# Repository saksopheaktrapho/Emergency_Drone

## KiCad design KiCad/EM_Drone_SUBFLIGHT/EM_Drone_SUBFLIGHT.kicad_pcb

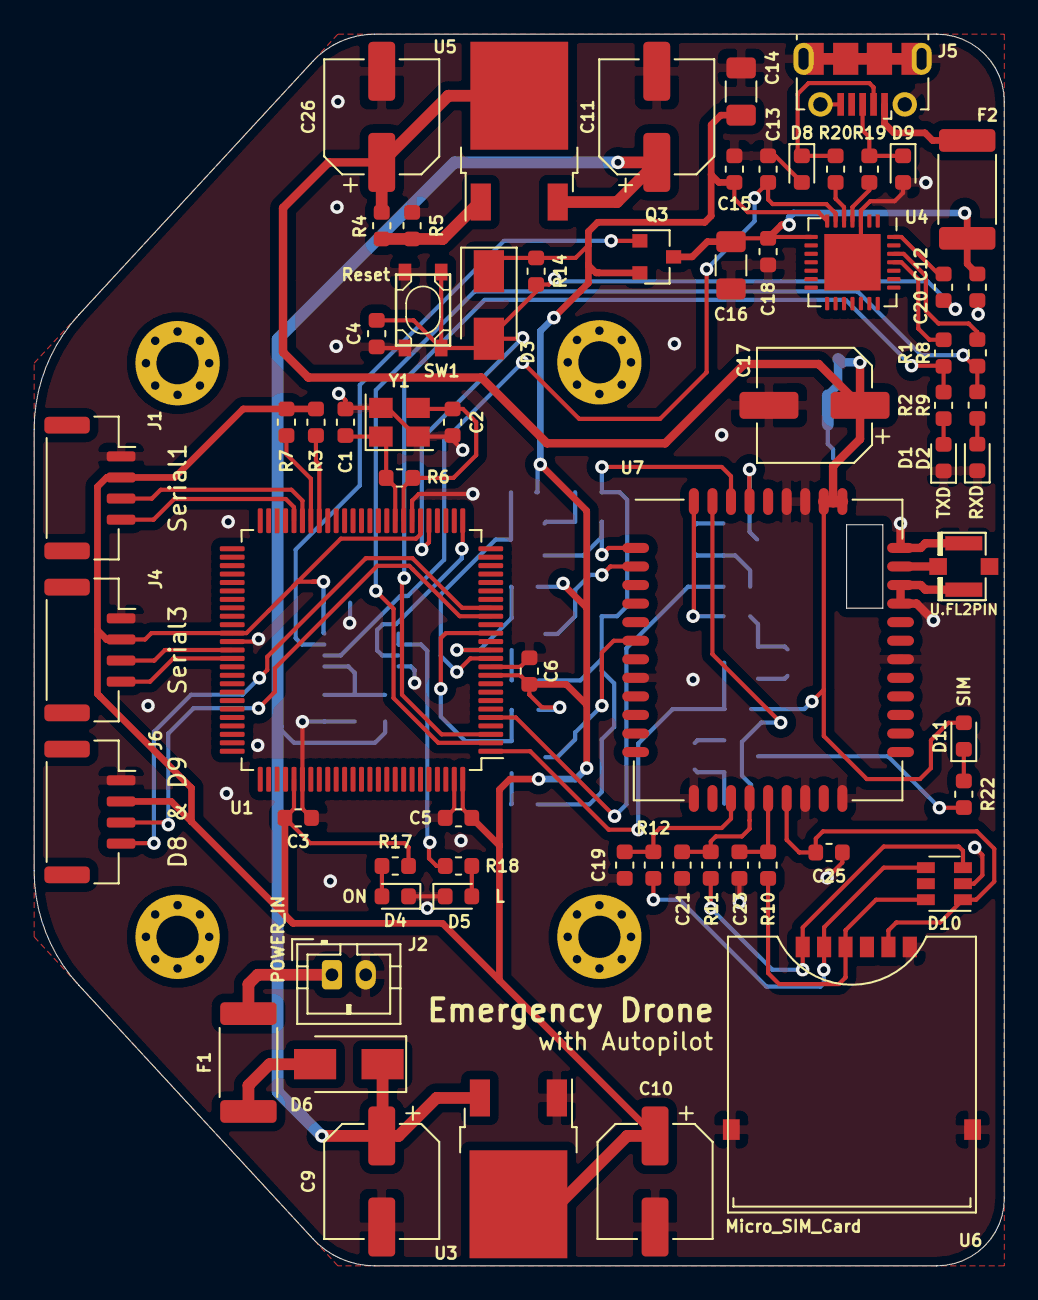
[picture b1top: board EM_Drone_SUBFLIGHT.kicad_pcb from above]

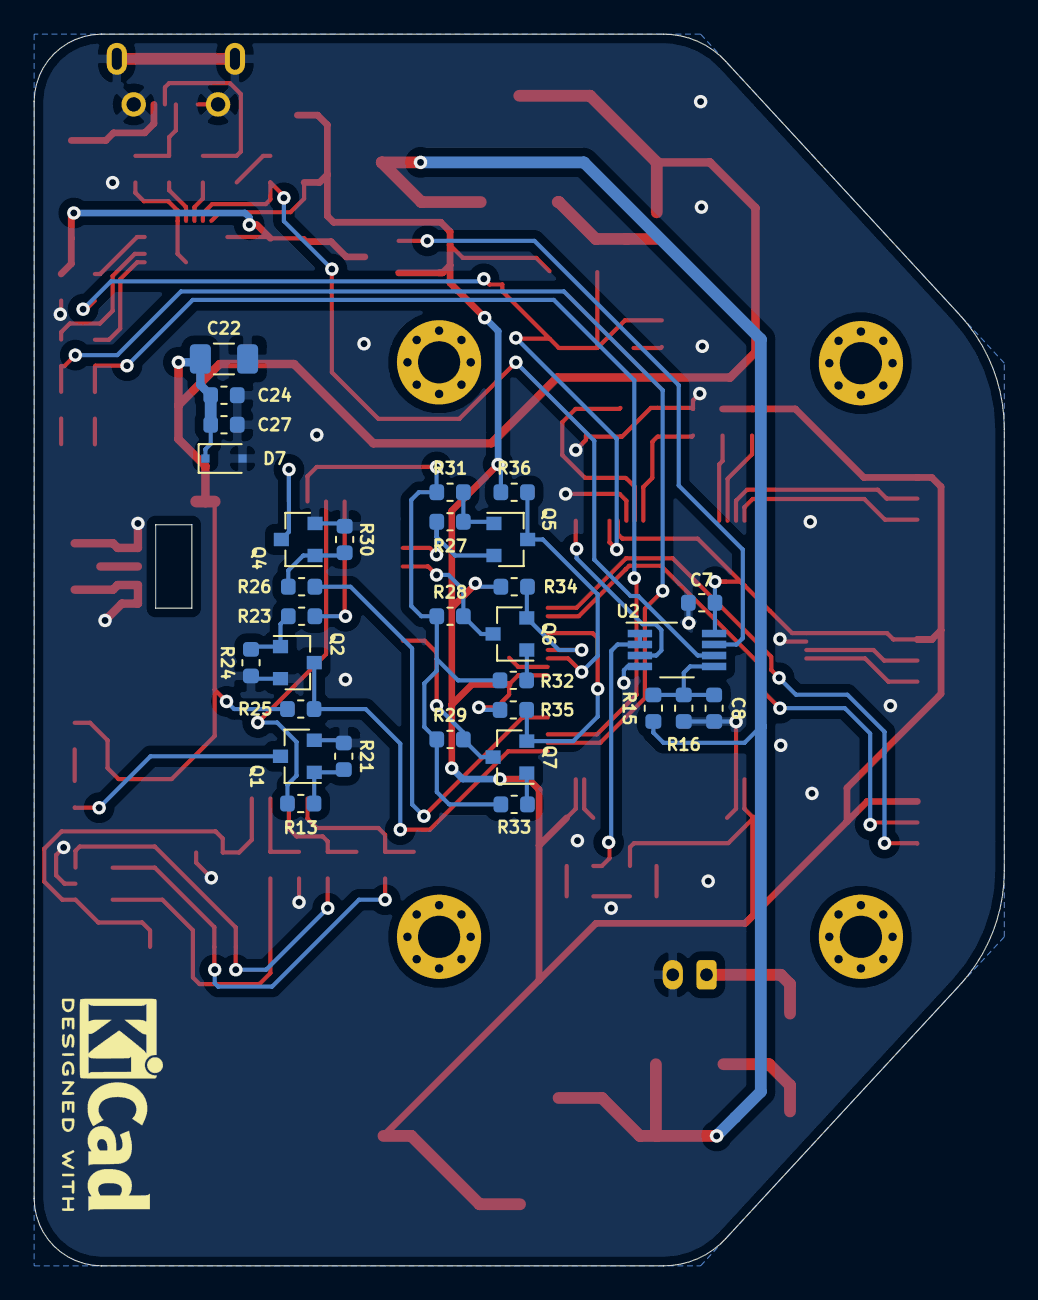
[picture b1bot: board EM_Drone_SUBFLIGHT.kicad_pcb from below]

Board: 2 copper layers, 57.5 x 73.0 mm, 102 parts (31 on the bottom side), 66 nets.

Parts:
C1, C2, C4, C19, C21, C23: 22p; C_0603_1608Metric
C3, C5, C6, C7, C8, C12, C13, C15, C18, C20, C25: 100n; C_0603_1608Metric
C9, C10, C11, C26: 470u; CP_Elec_6.3x7.7
C14, C16: 10u; C_1206_3216Metric
C17: CA_470u; CP_Elec_6.3x7.7
C22: CB_10u; C_1206_3216Metric
C24: 33p; C_0603_1608Metric
C27: 10p; C_0603_1608Metric
D1: TXD; LED_0603_1608Metric
D2: RXD; LED_0603_1608Metric
D3, D6: D; D_SMA
D4: ON; LED_0603_1608Metric
D5: L; LED_0603_1608Metric
D7: D_Zener; D_SOD-323F
D8, D9: ESD; D_0603_1608Metric
D10: ESDA6V1-5SC6; SOT-23-6
D11: SIM; LED_0603_1608Metric
F1: Fuse; Fuse_2512_6332Metric
F2: 0.5A; Fuse_2512_6332Metric
H1, H2, H3, H4: MountingHole; MountingHole_2.5mm_Pad_Via
J1: Telemetry_Port; JST_GH_SM04B-GHS-TB_1x04-1MP_P1.25mm_Horizontal
J2: POWER_IN; JST_PH_B2B-PH-K_1x02_P2.00mm_Vertical
J3: U.FL2PIN; U.FL
J4: Serial3; JST_GH_SM04B-GHS-TB_1x04-1MP_P1.25mm_Horizontal
J5: USB_B_Micro; USB_Micro-B_Molex-105017-0001
J6: IO; JST_GH_SM04B-GHS-TB_1x04-1MP_P1.25mm_Horizontal
Q1, Q2, Q4, Q5, Q6, Q7: 1P; SOT-23
Q3: FDN340P; SOT-23
R1, R2, R8, R9, R17, R18: 1k; R_0603_1608Metric
R3, R5, R7, R13, R23, R26, R28, R29, R31, R32, R33, R36: 4.7k; R_0603_1608Metric
R4: 2k; R_0603_1608Metric
R6: 1M; R_0603_1608Metric
R10, R11, R12: 510; R_0603_1608Metric
R14, R15, R16: 10k; R_0603_1608Metric
R19, R20: 22; R_0603_1608Metric
R21, R24, R27, R30, R34, R35: 47k; R_0603_1608Metric
R22, R25: 470; R_0603_1608Metric
SW1: SW_Push; Button_Switch_3.2x4.2
U1: ATmega2560-16AU; TQFP-100_14x14mm_P0.5mm
U2: LMV358; VSSOP-8_3.0x3.0mm_P0.65mm
U3: LM1084-5.0; TO-252-2
U4: CP2102N-A01-GQFN28; QFN-28-1EP_5x5mm_P0.5mm_EP3.35x3.35mm
U5: LM1084-ADJ; TO-252-2
U6: microSIM_Holder_0181AAAA06A
U7: SIM7020E; SIMCom_SIM800C
Y1: Crystal_GND24; Crystal_SMD_3225-4Pin_3.2x2.5mm

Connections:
+3V3: C13.1, U2.6, U4.6
+5V: C3.1, C5.1, C6.1, C7.1, C10.1, C14.1, C15.1, D3.1, J1.2, J4.2, J6.2, Q3.2, R3.1, R7.1, R14.1, R17.2, R34.1, R35.1, R36.1, U1.10, U1.31, U1.61, U1.80, U1.100, U2.8, U3.2, U4.7
/Arduino_MEGA/D4: Q2.3, R25.2, U1.1
/Arduino_MEGA/D5: R26.2, U1.5
/Arduino_MEGA/D6: Q7.2, R35.2, U1.15
/Arduino_MEGA/D8: J6.3, U1.17
/Arduino_MEGA/D9: J6.4, U1.18
/Arduino_MEGA/PB7: U1.26, U2.3
/Arduino_MEGA/RESET: C4.1, C12.2, D3.2, R14.2, SW1.1, U1.30
/Arduino_MEGA/RX0: R8.1, R9.2, U1.2
/Arduino_MEGA/RXD1: J1.3, U1.45
/Arduino_MEGA/RXD2: Q5.3, R36.2, U1.12
/Arduino_MEGA/RXD3: J4.3, U1.63
/Arduino_MEGA/SCL: R3.2, U1.43
/Arduino_MEGA/SDA: R7.2, U1.44
/Arduino_MEGA/TX0: R1.1, R2.2, U1.3
/Arduino_MEGA/TXD1: J1.4, U1.46
/Arduino_MEGA/TXD3: J4.4, U1.64
/Arduino_MEGA/U_RXD: R1.2, U4.25
/Arduino_MEGA/U_TXD: R8.2, U4.26
/Arduino_MEGA/XTAL1: C1.1, R6.1, U1.34, Y1.1
/Arduino_MEGA/XTAL2: C2.1, R6.2, U1.33, Y1.3
/SIM800c/GSM_ANT: J3.FEED, U7.32
/SIM800c/NETLIGHT: R13.2, U7.41
/SIM800c/PWRKEY: Q4.3, U7.39
/SIM800c/RXD: Q6.2, R34.2, U1.13
/SIM800c/SIM_CLK: C21.1, R11.2, U7.16
/SIM800c/SIM_DATA: C19.1, R12.2, U7.15
/SIM800c/SIM_RST: C23.1, R10.2, U7.17
/SIM800c/SIM_VDD: C25.1, D10.1, U6.C1, U7.18
/SIM800c/STATUS: R23.2, U7.42
/SIM800c/U1_DTR: Q7.3, R29.2, U7.6
/SIM800c/U1_RXD: Q6.3, R28.2, U7.2
/SIM800c/U1_TXD: Q5.2, R27.2, U7.1
/SIM800c/VBAT: C17.1, C22.1, C24.1, C26.1, C27.1, D7.1, D11.2, R4.1, R25.1, U5.2, U7.34, U7.35
GND: C1.2, C2.2, C3.2, C4.2, C5.2, C6.2, C7.2, C8.2, C9.2, C10.2, C11.2, C13.2, C14.2, C15.2, C16.2, C17.2, C18.2, C19.2, C20.2, C21.2, C22.2, C23.2, C24.2, C25.2, C26.2, C27.2, D1.1, D2.1, D4.1, D5.1, D7.2, D8.2, D9.2, D10.2, J1.1, J2.2, J3.1, J3.2, J4.1, J5.5, J5.6, J6.1, Q1.2, Q2.2, Q4.2, R5.2, R16.2, R21.2, R24.2, R30.2, SW1.2, U1.11, U1.32, U1.62, U1.81, U1.99, U2.4, U3.1, U4.3, U4.29, U6.C2, U6.MP, U7.8, U7.13, U7.19, U7.21, U7.27, U7.30, U7.31, U7.33, U7.36, U7.37, Y1.2, Y1.4
unnamed: C8.1, R15.2, R16.1, U2.5
unnamed: C12.1, U4.28
unnamed: D1.2, R2.1
unnamed: D2.2, R9.1
unnamed: D4.2, R17.1
unnamed: D5.2, R18.1
unnamed: D6.2, F1.1
unnamed: D8.1, J5.2, R20.1
unnamed: D9.1, J5.3, R19.1
unnamed: D10.3, R11.1, U6.C5
unnamed: D10.4, R12.1, U6.C6
unnamed: D10.6, R10.1, U6.C3
unnamed: D11.1, R22.1
unnamed: F1.2, J2.1
unnamed: F2.2, J5.1
unnamed: Q1.1, R13.1, R21.1
unnamed: Q1.3, R22.2
unnamed: Q2.1, R23.1, R24.1
unnamed: Q3.1, U2.7
unnamed: Q4.1, R26.1, R30.1
unnamed: Q5.1, R27.1, R31.2
unnamed: Q6.1, R32.2
unnamed: Q7.1, R33.2
unnamed: R4.2, R5.1, U5.1
unnamed: R18.2, U2.1, U2.2
unnamed: R19.2, U4.4
unnamed: R20.2, U4.5
VBUS: C16.1, C18.1, C20.1, F2.1, Q3.3, U4.8
VDD: R28.1, R29.1, R31.1, R32.1, R33.1, U7.40
VIN: C9.1, C11.1, D6.1, R15.1, U3.3, U5.3

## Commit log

2021-08-04 Add V2
2021-09-15 Add KiCad and Flutter Files
    Update_2
